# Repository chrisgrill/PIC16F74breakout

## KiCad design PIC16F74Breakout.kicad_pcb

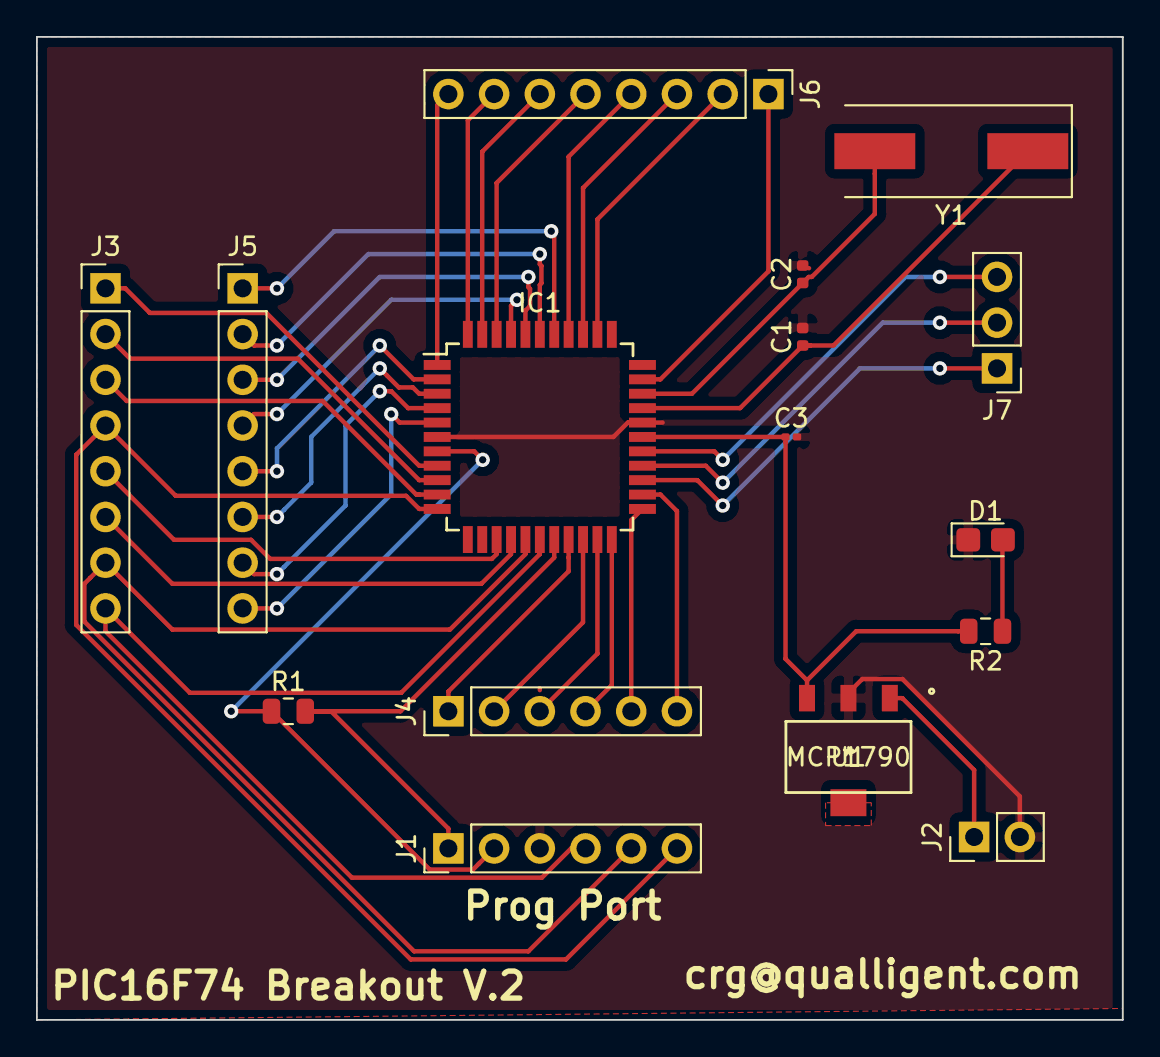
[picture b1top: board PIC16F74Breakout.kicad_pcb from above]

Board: 2 copper layers, 60.3 x 54.6 mm, 16 parts (0 on the bottom side), 41 nets.

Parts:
C1, C2: 15pf; C_0402_1005Metric
C3: 0.1uf; C_0201_0603Metric
D1: LED; LED_0805_2012Metric_Castellated
IC1: PIC16F74-I_PT; TQFP-44_10x10mm_P0.8mm
J1: Prog_Port; PinHeader_1x06_P2.54mm_Vertical
J2: Power; PinHeader_1x02_P2.54mm_Vertical
J3: PortB; PinHeader_1x08_P2.54mm_Vertical
J4: PortA; PinHeader_1x06_P2.54mm_Vertical
J5: PortD; PinHeader_1x08_P2.54mm_Vertical
J6: PortC; PinHeader_1x08_P2.54mm_Vertical
J7: PortE; PinHeader_1x03_P2.54mm_Vertical
R1: 4.7k; R_0805_2012Metric
R2: 10k; R_0805_2012Metric
U1: MCP1790; mcp1790-3302e&slash_db
Y1: Crystal; Crystal_SMD_HC49-SD

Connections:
GND: C1.2, C2.2, C3.2, D1.1, IC1.6, IC1.29, J1.3, J2.2, U1.2
unnamed: C1.1, IC1.30, Y1.1
unnamed: C2.1, IC1.31, Y1.2
unnamed: C3.1, IC1.28, R2.2, U1.3
unnamed: D1.2, R2.1
unnamed: IC1.1, J6.8
unnamed: IC1.2, J5.5
unnamed: IC1.3, J5.6
unnamed: IC1.4, J5.7
unnamed: IC1.5, J5.8
unnamed: IC1.7, J1.2, R1.1
unnamed: IC1.8, J3.1
unnamed: IC1.9, J3.2
unnamed: IC1.10, J3.3
unnamed: IC1.11, J1.6, J3.4
unnamed: IC1.14, J3.5
unnamed: IC1.15, J3.6
unnamed: IC1.16, J1.5, J3.7
unnamed: IC1.17, J1.4, J3.8
unnamed: IC1.18, J1.1, R1.2
unnamed: IC1.19, J4.1
unnamed: IC1.20, J4.2
unnamed: IC1.21, J4.3
unnamed: IC1.22, J4.4
unnamed: IC1.23, J4.5
unnamed: IC1.24, J4.6
unnamed: IC1.25, J7.1
unnamed: IC1.26, J7.2
unnamed: IC1.27, J7.3
unnamed: IC1.32, J6.1
unnamed: IC1.35, J6.2
unnamed: IC1.36, J6.3
unnamed: IC1.37, J6.4
unnamed: IC1.38, J5.1
unnamed: IC1.39, J5.2
unnamed: IC1.40, J5.3
unnamed: IC1.41, J5.4
unnamed: IC1.42, J6.5
unnamed: IC1.43, J6.6
unnamed: IC1.44, J6.7
unnamed: J2.1, U1.1

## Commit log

2021-02-24 Initial
2021-02-24 Add gitignore

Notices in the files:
parts and their libraries:
Copyright 2016 Accelerated Designs. All rights reserved.
